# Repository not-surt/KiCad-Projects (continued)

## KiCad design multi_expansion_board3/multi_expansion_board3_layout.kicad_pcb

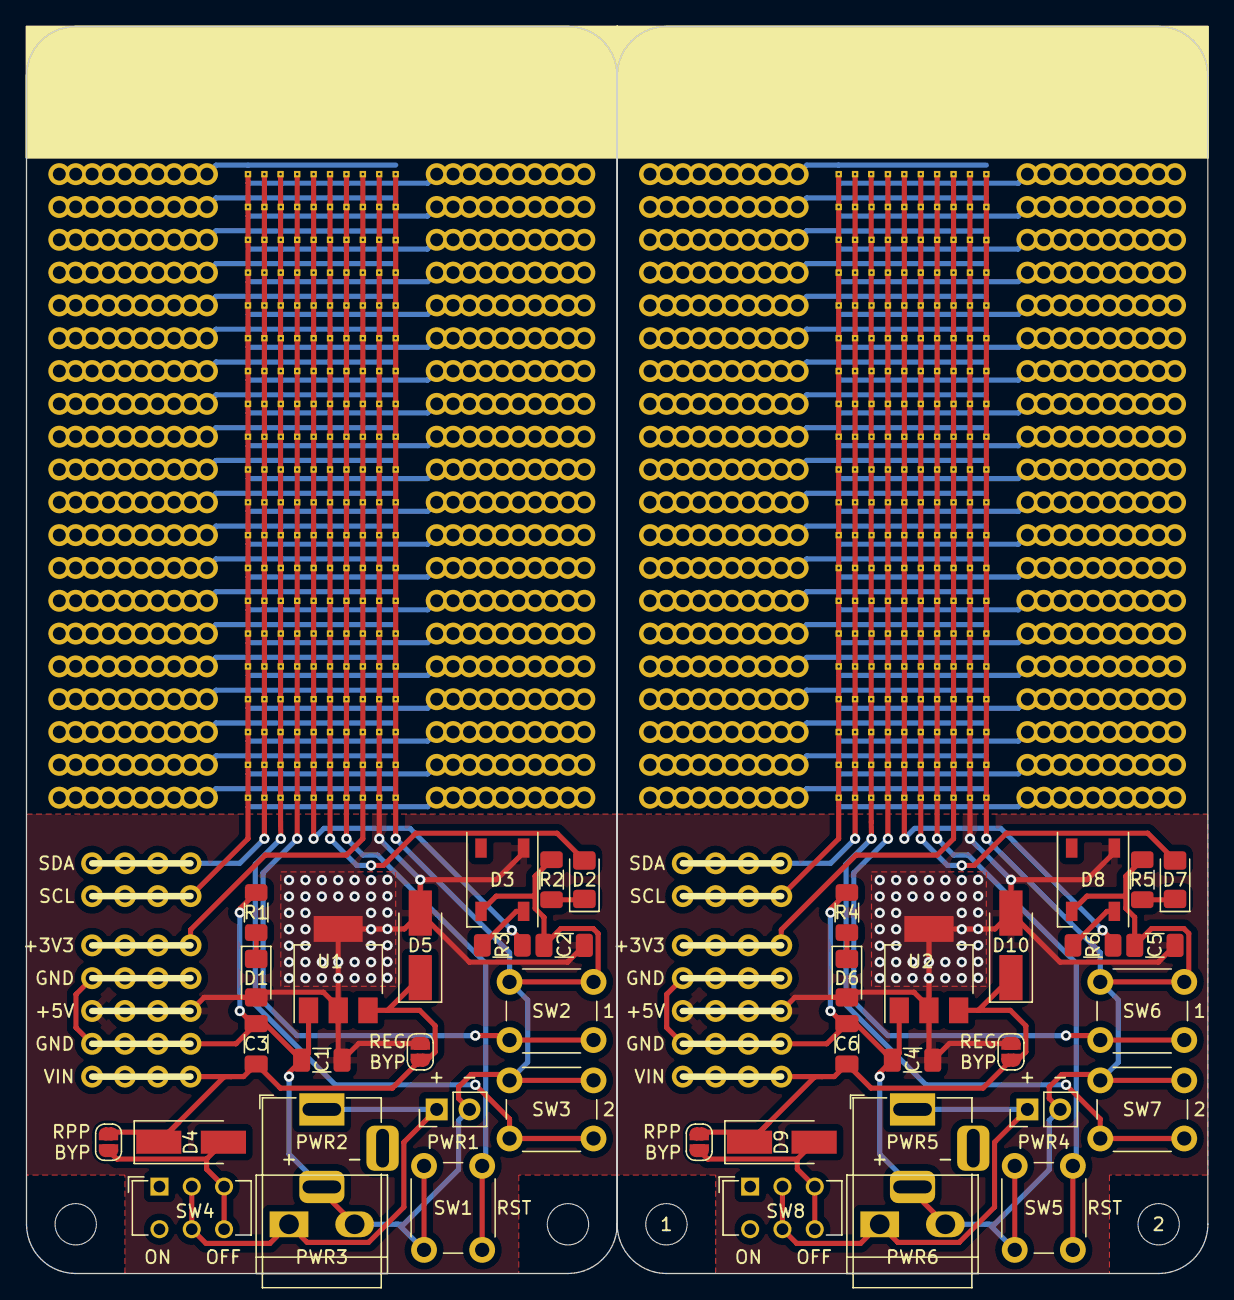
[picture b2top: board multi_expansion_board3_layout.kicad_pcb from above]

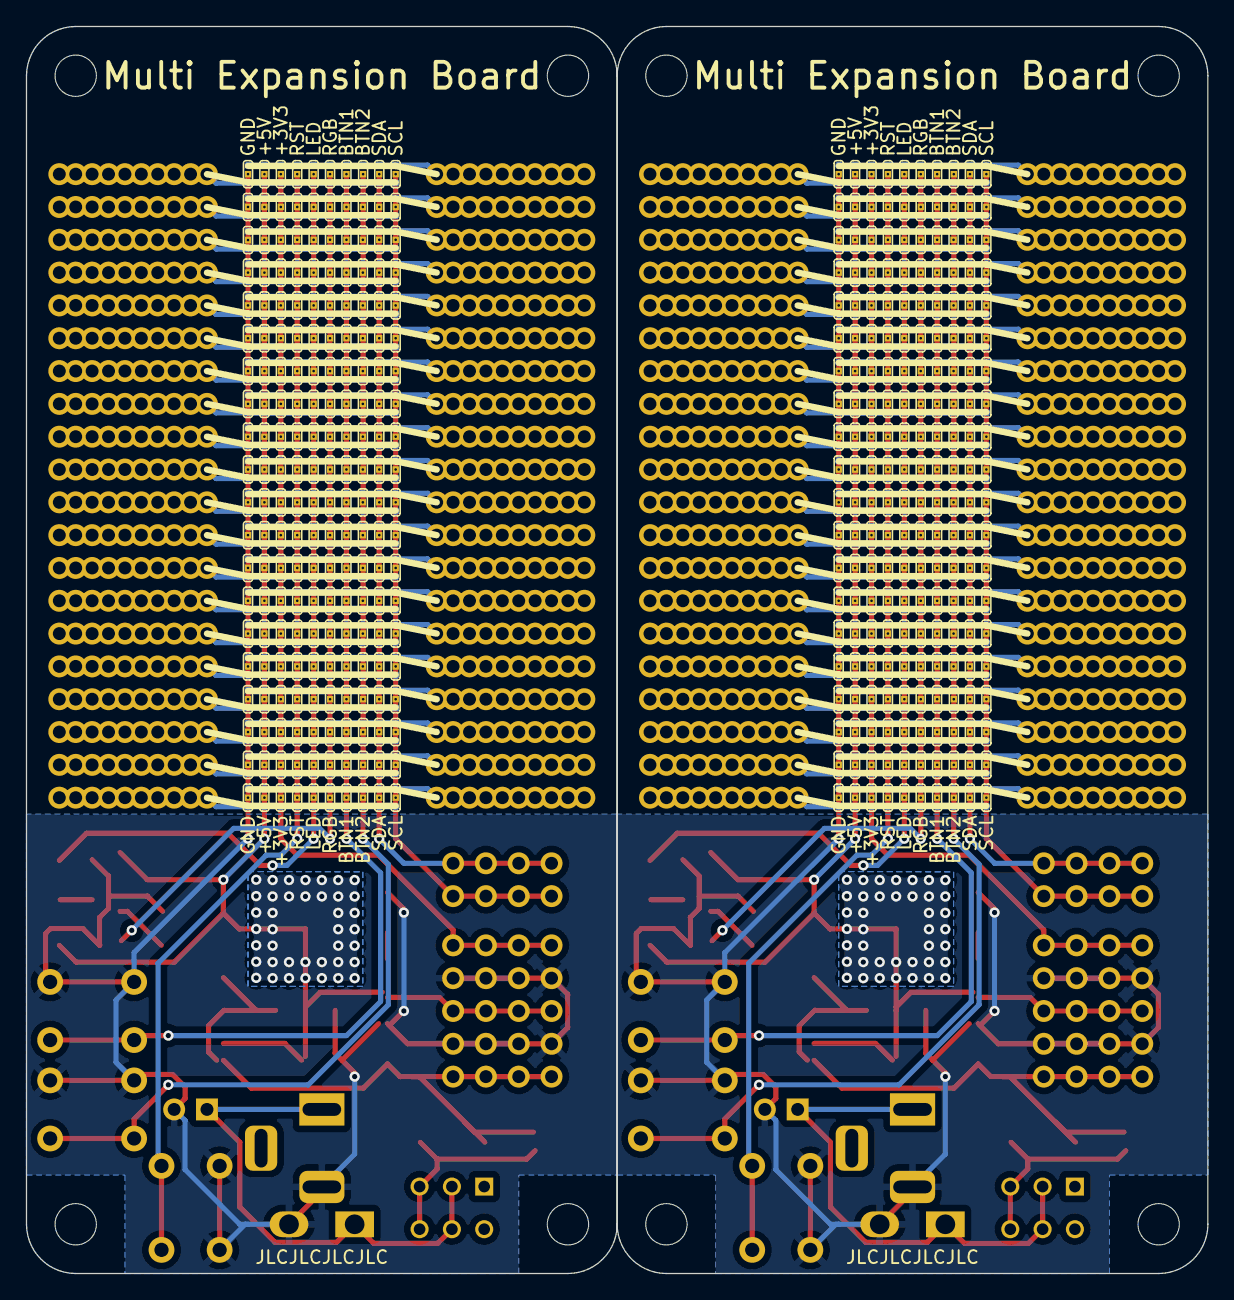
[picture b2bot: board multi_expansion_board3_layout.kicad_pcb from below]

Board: 2 copper layers, 91.4 x 96.5 mm, 500 parts (400 on the bottom side), 56 nets.

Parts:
1, 2, 3, 4: MountingHole_3.2mm_M3
C1, C4: 0.1uF; C_1206_3216Metric_Pad1.33x1.80mm_HandSolder
C2, C3, C5, C6: 10uF; C_1206_3216Metric_Pad1.33x1.80mm_HandSolder
D1, D2, D6, D7: LED; LED_1206_3216Metric_Pad1.42x1.75mm_HandSolder
D3, D8: WS2812B; LED_WS2812B_PLCC4_5.0x5.0mm_P3.2mm
D4, D5, D9, D10: D; D_SMA_Handsoldering
J1, J2, J3, J4, J5, J6, J7, J8, J9, J10, J11, J12, J13, J14, J15, J16, J17, J18, J19, J20, J28, J29, J30, J31, J32, J33, J34, J35, J36, J37, J38, J39, J40, J41, J42, J43, J44, J45, J46, J47: Conn_01x20; PinHeader_1x20_P2.54mm_Vertical_No_Silk
J21, J22, J23, J24, J25, J26, J27, J48, J49, J50, J51, J52, J53, J54: Conn_01x04; PinHeader_1x04_P2.54mm_Vertical_No_Silk
JP1, JP2, JP203, JP204: SolderJumper_2_Open; SolderJumper-2_P1.3mm_Open_RoundedPad1.0x1.5mm
JP3, JP4, JP5, JP6, JP7, JP8, JP9, JP10, JP11, JP12, JP13, JP14, JP15, JP16, JP17, JP18, JP19, JP20, JP21, JP22, JP23, JP24, JP25, JP26, JP27, JP28, JP29, JP30, JP31, JP32, JP33, JP34, JP35, JP36, JP37, JP38, JP39, JP40, JP41, JP42, JP43, JP44, JP45, JP46, JP47, JP48, JP49, JP50, JP51, JP52, JP53, JP54, JP55, JP56, JP57, JP58, JP59, JP60, JP61, JP62, JP63, JP64, JP65, JP66, JP67, JP68, JP69, JP70, JP71, JP72, JP73, JP74, JP75, JP76, JP77, JP78, JP79, JP80, JP81, JP82, JP83, JP84, JP85, JP86, JP87, JP88, JP89, JP90, JP91, JP92, JP93, JP94, JP95, JP96, JP97, JP98, JP99, JP100, JP101, JP102, JP103, JP104, JP105, JP106, JP107, JP108, JP109, JP110, JP111, JP112, JP113, JP114, JP115, JP116, JP117, JP118, JP119, JP120, JP121, JP122, JP123, JP124, JP125, JP126, JP127, JP128, JP129, JP130, JP131, JP132, JP133, JP134, JP135, JP136, JP137, JP138, JP139, JP140, JP141, JP142, JP143, JP144, JP145, JP146, JP147, JP148, JP149, JP150, JP151, JP152, JP153, JP154, JP155, JP156, JP157, JP158, JP159, JP160, JP161, JP162, JP163, JP164, JP165, JP166, JP167, JP168, JP169, JP170, JP171, JP172, JP173, JP174, JP175, JP176, JP177, JP178, JP179, JP180, JP181, JP182, JP183, JP184, JP185, JP186, JP187, JP188, JP189, JP190, JP191, JP192, JP193, JP194, JP195, JP196, JP197, JP198, JP199, JP200, JP201, JP202, JP205, JP206, JP207, JP208, JP209, JP210, JP211, JP212, JP213, JP214, JP215, JP216, JP217, JP218, JP219, JP220, JP221, JP222, JP223, JP224, JP225, JP226, JP227, JP228, JP229, JP230, JP231, JP232, JP233, JP234, JP235, JP236, JP237, JP238, JP239, JP240, JP241, JP242, JP243, JP244, JP245, JP246, JP247, JP248, JP249, JP250, JP251, JP252, JP253, JP254, JP255, JP256, JP257, JP258, JP259, JP260, JP261, JP262, JP263, JP264, JP265, JP266, JP267, JP268, JP269, JP270, JP271, JP272, JP273, JP274, JP275, JP276, JP277, JP278, JP279, JP280, JP281, JP282, JP283, JP284, JP285, JP286, JP287, JP288, JP289, JP290, JP291, JP292, JP293, JP294, JP295, JP296, JP297, JP298, JP299, JP300, JP301, JP302, JP303, JP304, JP305, JP306, JP307, JP308, JP309, JP310, JP311, JP312, JP313, JP314, JP315, JP316, JP317, JP318, JP319, JP320, JP321, JP322, JP323, JP324, JP325, JP326, JP327, JP328, JP329, JP330, JP331, JP332, JP333, JP334, JP335, JP336, JP337, JP338, JP339, JP340, JP341, JP342, JP343, JP344, JP345, JP346, JP347, JP348, JP349, JP350, JP351, JP352, JP353, JP354, JP355, JP356, JP357, JP358, JP359, JP360, JP361, JP362, JP363, JP364, JP365, JP366, JP367, JP368, JP369, JP370, JP371, JP372, JP373, JP374, JP375, JP376, JP377, JP378, JP379, JP380, JP381, JP382, JP383, JP384, JP385, JP386, JP387, JP388, JP389, JP390, JP391, JP392, JP393, JP394, JP395, JP396, JP397, JP398, JP399, JP400, JP401, JP402, JP403, JP404: SolderJumper_3_Open; SolderJumper-mini-3
PWR1, PWR4: Conn_01x02; PinHeader_1x02_P2.54mm_Vertical
PWR2, PWR5: Barrel_Jack; BarrelJack_Horizontal
PWR3, PWR6: Screw_Terminal_01x02; TerminalBlock_bornier-2_P5.08mm
R1, R2, R4, R5: R; R_1206_3216Metric_Pad1.30x1.75mm_HandSolder
R3, R6: 470R; R_1206_3216Metric_Pad1.30x1.75mm_HandSolder
SW1, SW2, SW3, SW5, SW6, SW7: SW_Push; SW_PUSH_6mm
SW4, SW8: SW_SPST; SW_CuK_JS202011CQN_DPDT_Straight
U1, U2: AMS1117-5.0; SOT-223-3_TabPin2

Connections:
/+3V3: J25.1, J25.2, J25.3, J25.4, J52.1, J52.2, J52.3, J52.4, JP43.2 (C), JP44.2 (C), JP45.2 (C), JP46.2 (C), JP47.2 (C), JP48.2 (C), JP49.2 (C), JP50.2 (C), JP51.2 (C), JP52.2 (C), JP53.2 (C), JP54.2 (C), JP55.2 (C), JP56.2 (C), JP57.2 (C), JP58.2 (C), JP59.2 (C), JP60.2 (C), JP61.2 (C), JP62.2 (C), JP245.2 (C), JP246.2 (C), JP247.2 (C), JP248.2 (C), JP249.2 (C), JP250.2 (C), JP251.2 (C), JP252.2 (C), JP253.2 (C), JP254.2 (C), JP255.2 (C), JP256.2 (C), JP257.2 (C), JP258.2 (C), JP259.2 (C), JP260.2 (C), JP261.2 (C), JP262.2 (C), JP263.2 (C), JP264.2 (C)
/+5V: C1.2, C2.1, C4.2, C5.1, D1.2 (A), D3.1 (VDD), D5.2 (A), D6.2 (A), D8.1 (VDD), D10.2 (A), J24.1, J24.2, J24.3, J24.4, J51.1, J51.2, J51.3, J51.4, JP2.2 (B), JP3.2 (C), JP4.2 (C), JP5.2 (C), JP6.2 (C), JP7.2 (C), JP8.2 (C), JP9.2 (C), JP10.2 (C), JP11.2 (C), JP12.2 (C), JP13.2 (C), JP14.2 (C), JP15.2 (C), JP16.2 (C), JP17.2 (C), JP18.2 (C), JP19.2 (C), JP20.2 (C), JP21.2 (C), JP22.2 (C), JP204.2 (B), JP205.2 (C), JP206.2 (C), JP207.2 (C), JP208.2 (C), JP209.2 (C), JP210.2 (C), JP211.2 (C), JP212.2 (C), JP213.2 (C), JP214.2 (C), JP215.2 (C), JP216.2 (C), JP217.2 (C), JP218.2 (C), JP219.2 (C), JP220.2 (C), JP221.2 (C), JP222.2 (C), JP223.2 (C), JP224.2 (C), U1.2 (VO), U2.2 (VO)
/BTN1: JP83.2 (C), JP84.2 (C), JP85.2 (C), JP86.2 (C), JP87.2 (C), JP88.2 (C), JP89.2 (C), JP90.2 (C), JP91.2 (C), JP92.2 (C), JP93.2 (C), JP94.2 (C), JP95.2 (C), JP96.2 (C), JP97.2 (C), JP98.2 (C), JP99.2 (C), JP100.2 (C), JP101.2 (C), JP102.2 (C), JP285.2 (C), JP286.2 (C), JP287.2 (C), JP288.2 (C), JP289.2 (C), JP290.2 (C), JP291.2 (C), JP292.2 (C), JP293.2 (C), JP294.2 (C), JP295.2 (C), JP296.2 (C), JP297.2 (C), JP298.2 (C), JP299.2 (C), JP300.2 (C), JP301.2 (C), JP302.2 (C), JP303.2 (C), JP304.2 (C), SW2.2, SW6.2
/BTN2: JP183.2 (C), JP184.2 (C), JP185.2 (C), JP186.2 (C), JP187.2 (C), JP188.2 (C), JP189.2 (C), JP190.2 (C), JP191.2 (C), JP192.2 (C), JP193.2 (C), JP194.2 (C), JP195.2 (C), JP196.2 (C), JP197.2 (C), JP198.2 (C), JP199.2 (C), JP200.2 (C), JP201.2 (C), JP202.2 (C), JP385.2 (C), JP386.2 (C), JP387.2 (C), JP388.2 (C), JP389.2 (C), JP390.2 (C), JP391.2 (C), JP392.2 (C), JP393.2 (C), JP394.2 (C), JP395.2 (C), JP396.2 (C), JP397.2 (C), JP398.2 (C), JP399.2 (C), JP400.2 (C), JP401.2 (C), JP402.2 (C), JP403.2 (C), JP404.2 (C), SW3.2, SW7.2
/LED: D2.2 (A), D7.2 (A), JP63.2 (C), JP64.2 (C), JP65.2 (C), JP66.2 (C), JP67.2 (C), JP68.2 (C), JP69.2 (C), JP70.2 (C), JP71.2 (C), JP72.2 (C), JP73.2 (C), JP74.2 (C), JP75.2 (C), JP76.2 (C), JP77.2 (C), JP78.2 (C), JP79.2 (C), JP80.2 (C), JP81.2 (C), JP82.2 (C), JP265.2 (C), JP266.2 (C), JP267.2 (C), JP268.2 (C), JP269.2 (C), JP270.2 (C), JP271.2 (C), JP272.2 (C), JP273.2 (C), JP274.2 (C), JP275.2 (C), JP276.2 (C), JP277.2 (C), JP278.2 (C), JP279.2 (C), JP280.2 (C), JP281.2 (C), JP282.2 (C), JP283.2 (C), JP284.2 (C)
/RGB: JP103.2 (C), JP104.2 (C), JP105.2 (C), JP106.2 (C), JP107.2 (C), JP108.2 (C), JP109.2 (C), JP110.2 (C), JP111.2 (C), JP112.2 (C), JP113.2 (C), JP114.2 (C), JP115.2 (C), JP116.2 (C), JP117.2 (C), JP118.2 (C), JP119.2 (C), JP120.2 (C), JP121.2 (C), JP122.2 (C), JP305.2 (C), JP306.2 (C), JP307.2 (C), JP308.2 (C), JP309.2 (C), JP310.2 (C), JP311.2 (C), JP312.2 (C), JP313.2 (C), JP314.2 (C), JP315.2 (C), JP316.2 (C), JP317.2 (C), JP318.2 (C), JP319.2 (C), JP320.2 (C), JP321.2 (C), JP322.2 (C), JP323.2 (C), JP324.2 (C), R3.1, R6.1
/RST: JP163.2 (C), JP164.2 (C), JP165.2 (C), JP166.2 (C), JP167.2 (C), JP168.2 (C), JP169.2 (C), JP170.2 (C), JP171.2 (C), JP172.2 (C), JP173.2 (C), JP174.2 (C), JP175.2 (C), JP176.2 (C), JP177.2 (C), JP178.2 (C), JP179.2 (C), JP180.2 (C), JP181.2 (C), JP182.2 (C), JP365.2 (C), JP366.2 (C), JP367.2 (C), JP368.2 (C), JP369.2 (C), JP370.2 (C), JP371.2 (C), JP372.2 (C), JP373.2 (C), JP374.2 (C), JP375.2 (C), JP376.2 (C), JP377.2 (C), JP378.2 (C), JP379.2 (C), JP380.2 (C), JP381.2 (C), JP382.2 (C), JP383.2 (C), JP384.2 (C), SW1.2, SW5.2
/SCL: J27.1, J27.2, J27.3, J27.4, J54.1, J54.2, J54.3, J54.4, JP143.2 (C), JP144.2 (C), JP145.2 (C), JP146.2 (C), JP147.2 (C), JP148.2 (C), JP149.2 (C), JP150.2 (C), JP151.2 (C), JP152.2 (C), JP153.2 (C), JP154.2 (C), JP155.2 (C), JP156.2 (C), JP157.2 (C), JP158.2 (C), JP159.2 (C), JP160.2 (C), JP161.2 (C), JP162.2 (C), JP345.2 (C), JP346.2 (C), JP347.2 (C), JP348.2 (C), JP349.2 (C), JP350.2 (C), JP351.2 (C), JP352.2 (C), JP353.2 (C), JP354.2 (C), JP355.2 (C), JP356.2 (C), JP357.2 (C), JP358.2 (C), JP359.2 (C), JP360.2 (C), JP361.2 (C), JP362.2 (C), JP363.2 (C), JP364.2 (C)
/SDA: J26.1, J26.2, J26.3, J26.4, J53.1, J53.2, J53.3, J53.4, JP123.2 (C), JP124.2 (C), JP125.2 (C), JP126.2 (C), JP127.2 (C), JP128.2 (C), JP129.2 (C), JP130.2 (C), JP131.2 (C), JP132.2 (C), JP133.2 (C), JP134.2 (C), JP135.2 (C), JP136.2 (C), JP137.2 (C), JP138.2 (C), JP139.2 (C), JP140.2 (C), JP141.2 (C), JP142.2 (C), JP325.2 (C), JP326.2 (C), JP327.2 (C), JP328.2 (C), JP329.2 (C), JP330.2 (C), JP331.2 (C), JP332.2 (C), JP333.2 (C), JP334.2 (C), JP335.2 (C), JP336.2 (C), JP337.2 (C), JP338.2 (C), JP339.2 (C), JP340.2 (C), JP341.2 (C), JP342.2 (C), JP343.2 (C), JP344.2 (C)
/VIN: C3.1, C6.1, D4.1 (K), D5.1 (K), D9.1 (K), D10.1 (K), J23.1, J23.2, J23.3, J23.4, J50.1, J50.2, J50.3, J50.4, JP1.2 (B), JP2.1 (A), JP203.2 (B), JP204.1 (A), U1.3 (VI), U2.3 (VI)
GND: C1.1, C2.2, C3.2, C4.1, C5.2, C6.2, D3.3 (VSS), D8.3 (VSS), J21.1, J21.2, J21.3, J21.4, J22.1, J22.2, J22.3, J22.4, J48.1, J48.2, J48.3, J48.4, J49.1, J49.2, J49.3, J49.4, JP23.2 (C), JP24.2 (C), JP25.2 (C), JP26.2 (C), JP27.2 (C), JP28.2 (C), JP29.2 (C), JP30.2 (C), JP31.2 (C), JP32.2 (C), JP33.2 (C), JP34.2 (C), JP35.2 (C), JP36.2 (C), JP37.2 (C), JP38.2 (C), JP39.2 (C), JP40.2 (C), JP41.2 (C), JP42.2 (C), JP225.2 (C), JP226.2 (C), JP227.2 (C), JP228.2 (C), JP229.2 (C), JP230.2 (C), JP231.2 (C), JP232.2 (C), JP233.2 (C), JP234.2 (C), JP235.2 (C), JP236.2 (C), JP237.2 (C), JP238.2 (C), JP239.2 (C), JP240.2 (C), JP241.2 (C), JP242.2 (C), JP243.2 (C), JP244.2 (C), PWR1.2, PWR2.2, PWR3.2, PWR4.2, PWR5.2, PWR6.2, R1.2, R2.2, R4.2, R5.2, SW1.1, SW2.1, SW3.1, SW5.1, SW6.1, SW7.1, U1.1 (GND), U2.1 (GND)
unnamed: D1.1 (K), D6.1 (K), R1.1, R4.1
unnamed: D2.1 (K), D7.1 (K), R2.1, R5.1
unnamed: D3.4 (DIN), D8.4 (DIN), R3.2, R6.2
unnamed: D4.2 (A), D9.2 (A), JP1.1 (A), JP203.1 (A), SW4.3 (C), SW4.6 (C), SW8.3 (C), SW8.6 (C)
unnamed: PWR1.1, PWR2.1, PWR3.1, PWR4.1, PWR5.1, PWR6.1, SW4.2 (B), SW4.5 (B), SW8.2 (B), SW8.5 (B)
Pin_1: J1.1, J2.1, J3.1, J4.1, J5.1, J6.1, J7.1, J8.1, J9.1, J10.1, J28.1, J29.1, J30.1, J31.1, J32.1, J33.1, J34.1, J35.1, J36.1, J37.1, JP3.1 (A), JP23.1 (A), JP43.1 (A), JP63.1 (A), JP83.1 (A), JP103.1 (A), JP123.1 (A), JP143.1 (A), JP163.1 (A), JP183.1 (A), JP205.1 (A), JP225.1 (A), JP245.1 (A), JP265.1 (A), JP285.1 (A), JP305.1 (A), JP325.1 (A), JP345.1 (A), JP365.1 (A), JP385.1 (A)
Pin_2: J1.2, J2.2, J3.2, J4.2, J5.2, J6.2, J7.2, J8.2, J9.2, J10.2, J28.2, J29.2, J30.2, J31.2, J32.2, J33.2, J34.2, J35.2, J36.2, J37.2, JP4.1 (A), JP24.1 (A), JP44.1 (A), JP64.1 (A), JP84.1 (A), JP104.1 (A), JP124.1 (A), JP144.1 (A), JP164.1 (A), JP184.1 (A), JP206.1 (A), JP226.1 (A), JP246.1 (A), JP266.1 (A), JP286.1 (A), JP306.1 (A), JP326.1 (A), JP346.1 (A), JP366.1 (A), JP386.1 (A)
Pin_3: J1.3, J2.3, J3.3, J4.3, J5.3, J6.3, J7.3, J8.3, J9.3, J10.3, J28.3, J29.3, J30.3, J31.3, J32.3, J33.3, J34.3, J35.3, J36.3, J37.3, JP5.1 (A), JP25.1 (A), JP45.1 (A), JP65.1 (A), JP85.1 (A), JP105.1 (A), JP125.1 (A), JP145.1 (A), JP165.1 (A), JP185.1 (A), JP207.1 (A), JP227.1 (A), JP247.1 (A), JP267.1 (A), JP287.1 (A), JP307.1 (A), JP327.1 (A), JP347.1 (A), JP367.1 (A), JP387.1 (A)
Pin_4: J1.4, J2.4, J3.4, J4.4, J5.4, J6.4, J7.4, J8.4, J9.4, J10.4, J28.4, J29.4, J30.4, J31.4, J32.4, J33.4, J34.4, J35.4, J36.4, J37.4, JP6.1 (A), JP26.1 (A), JP46.1 (A), JP66.1 (A), JP86.1 (A), JP106.1 (A), JP126.1 (A), JP146.1 (A), JP166.1 (A), JP186.1 (A), JP208.1 (A), JP228.1 (A), JP248.1 (A), JP268.1 (A), JP288.1 (A), JP308.1 (A), JP328.1 (A), JP348.1 (A), JP368.1 (A), JP388.1 (A)
Pin_5: J1.5, J2.5, J3.5, J4.5, J5.5, J6.5, J7.5, J8.5, J9.5, J10.5, J28.5, J29.5, J30.5, J31.5, J32.5, J33.5, J34.5, J35.5, J36.5, J37.5, JP7.1 (A), JP27.1 (A), JP47.1 (A), JP67.1 (A), JP87.1 (A), JP107.1 (A), JP127.1 (A), JP147.1 (A), JP167.1 (A), JP187.1 (A), JP209.1 (A), JP229.1 (A), JP249.1 (A), JP269.1 (A), JP289.1 (A), JP309.1 (A), JP329.1 (A), JP349.1 (A), JP369.1 (A), JP389.1 (A)
Pin_6: J1.6, J2.6, J3.6, J4.6, J5.6, J6.6, J7.6, J8.6, J9.6, J10.6, J28.6, J29.6, J30.6, J31.6, J32.6, J33.6, J34.6, J35.6, J36.6, J37.6, JP8.1 (A), JP28.1 (A), JP48.1 (A), JP68.1 (A), JP88.1 (A), JP108.1 (A), JP128.1 (A), JP148.1 (A), JP168.1 (A), JP188.1 (A), JP210.1 (A), JP230.1 (A), JP250.1 (A), JP270.1 (A), JP290.1 (A), JP310.1 (A), JP330.1 (A), JP350.1 (A), JP370.1 (A), JP390.1 (A)
Pin_7: J1.7, J2.7, J3.7, J4.7, J5.7, J6.7, J7.7, J8.7, J9.7, J10.7, J28.7, J29.7, J30.7, J31.7, J32.7, J33.7, J34.7, J35.7, J36.7, J37.7, JP9.1 (A), JP29.1 (A), JP49.1 (A), JP69.1 (A), JP89.1 (A), JP109.1 (A), JP129.1 (A), JP149.1 (A), JP169.1 (A), JP189.1 (A), JP211.1 (A), JP231.1 (A), JP251.1 (A), JP271.1 (A), JP291.1 (A), JP311.1 (A), JP331.1 (A), JP351.1 (A), JP371.1 (A), JP391.1 (A)
Pin_8: J1.8, J2.8, J3.8, J4.8, J5.8, J6.8, J7.8, J8.8, J9.8, J10.8, J28.8, J29.8, J30.8, J31.8, J32.8, J33.8, J34.8, J35.8, J36.8, J37.8, JP10.1 (A), JP30.1 (A), JP50.1 (A), JP70.1 (A), JP90.1 (A), JP110.1 (A), JP130.1 (A), JP150.1 (A), JP170.1 (A), JP190.1 (A), JP212.1 (A), JP232.1 (A), JP252.1 (A), JP272.1 (A), JP292.1 (A), JP312.1 (A), JP332.1 (A), JP352.1 (A), JP372.1 (A), JP392.1 (A)
Pin_9: J1.9, J2.9, J3.9, J4.9, J5.9, J6.9, J7.9, J8.9, J9.9, J10.9, J28.9, J29.9, J30.9, J31.9, J32.9, J33.9, J34.9, J35.9, J36.9, J37.9, JP11.1 (A), JP31.1 (A), JP51.1 (A), JP71.1 (A), JP91.1 (A), JP111.1 (A), JP131.1 (A), JP151.1 (A), JP171.1 (A), JP191.1 (A), JP213.1 (A), JP233.1 (A), JP253.1 (A), JP273.1 (A), JP293.1 (A), JP313.1 (A), JP333.1 (A), JP353.1 (A), JP373.1 (A), JP393.1 (A)
Pin_10: J1.10, J2.10, J3.10, J4.10, J5.10, J6.10, J7.10, J8.10, J9.10, J10.10, J28.10, J29.10, J30.10, J31.10, J32.10, J33.10, J34.10, J35.10, J36.10, J37.10, JP12.1 (A), JP32.1 (A), JP52.1 (A), JP72.1 (A), JP92.1 (A), JP112.1 (A), JP132.1 (A), JP152.1 (A), JP172.1 (A), JP192.1 (A), JP214.1 (A), JP234.1 (A), JP254.1 (A), JP274.1 (A), JP294.1 (A), JP314.1 (A), JP334.1 (A), JP354.1 (A), JP374.1 (A), JP394.1 (A)
Pin_11: J1.11, J2.11, J3.11, J4.11, J5.11, J6.11, J7.11, J8.11, J9.11, J10.11, J28.11, J29.11, J30.11, J31.11, J32.11, J33.11, J34.11, J35.11, J36.11, J37.11, JP13.1 (A), JP33.1 (A), JP53.1 (A), JP73.1 (A), JP93.1 (A), JP113.1 (A), JP133.1 (A), JP153.1 (A), JP173.1 (A), JP193.1 (A), JP215.1 (A), JP235.1 (A), JP255.1 (A), JP275.1 (A), JP295.1 (A), JP315.1 (A), JP335.1 (A), JP355.1 (A), JP375.1 (A), JP395.1 (A)
Pin_12: J1.12, J2.12, J3.12, J4.12, J5.12, J6.12, J7.12, J8.12, J9.12, J10.12, J28.12, J29.12, J30.12, J31.12, J32.12, J33.12, J34.12, J35.12, J36.12, J37.12, JP14.1 (A), JP34.1 (A), JP54.1 (A), JP74.1 (A), JP94.1 (A), JP114.1 (A), JP134.1 (A), JP154.1 (A), JP174.1 (A), JP194.1 (A), JP216.1 (A), JP236.1 (A), JP256.1 (A), JP276.1 (A), JP296.1 (A), JP316.1 (A), JP336.1 (A), JP356.1 (A), JP376.1 (A), JP396.1 (A)
Pin_13: J1.13, J2.13, J3.13, J4.13, J5.13, J6.13, J7.13, J8.13, J9.13, J10.13, J28.13, J29.13, J30.13, J31.13, J32.13, J33.13, J34.13, J35.13, J36.13, J37.13, JP15.1 (A), JP35.1 (A), JP55.1 (A), JP75.1 (A), JP95.1 (A), JP115.1 (A), JP135.1 (A), JP155.1 (A), JP175.1 (A), JP195.1 (A), JP217.1 (A), JP237.1 (A), JP257.1 (A), JP277.1 (A), JP297.1 (A), JP317.1 (A), JP337.1 (A), JP357.1 (A), JP377.1 (A), JP397.1 (A)
Pin_14: J1.14, J2.14, J3.14, J4.14, J5.14, J6.14, J7.14, J8.14, J9.14, J10.14, J28.14, J29.14, J30.14, J31.14, J32.14, J33.14, J34.14, J35.14, J36.14, J37.14, JP16.1 (A), JP36.1 (A), JP56.1 (A), JP76.1 (A), JP96.1 (A), JP116.1 (A), JP136.1 (A), JP156.1 (A), JP176.1 (A), JP196.1 (A), JP218.1 (A), JP238.1 (A), JP258.1 (A), JP278.1 (A), JP298.1 (A), JP318.1 (A), JP338.1 (A), JP358.1 (A), JP378.1 (A), JP398.1 (A)
Pin_15: J1.15, J2.15, J3.15, J4.15, J5.15, J6.15, J7.15, J8.15, J9.15, J10.15, J28.15, J29.15, J30.15, J31.15, J32.15, J33.15, J34.15, J35.15, J36.15, J37.15, JP17.1 (A), JP37.1 (A), JP57.1 (A), JP77.1 (A), JP97.1 (A), JP117.1 (A), JP137.1 (A), JP157.1 (A), JP177.1 (A), JP197.1 (A), JP219.1 (A), JP239.1 (A), JP259.1 (A), JP279.1 (A), JP299.1 (A), JP319.1 (A), JP339.1 (A), JP359.1 (A), JP379.1 (A), JP399.1 (A)
Pin_16: J1.16, J2.16, J3.16, J4.16, J5.16, J6.16, J7.16, J8.16, J9.16, J10.16, J28.16, J29.16, J30.16, J31.16, J32.16, J33.16, J34.16, J35.16, J36.16, J37.16, JP18.1 (A), JP38.1 (A), JP58.1 (A), JP78.1 (A), JP98.1 (A), JP118.1 (A), JP138.1 (A), JP158.1 (A), JP178.1 (A), JP198.1 (A), JP220.1 (A), JP240.1 (A), JP260.1 (A), JP280.1 (A), JP300.1 (A), JP320.1 (A), JP340.1 (A), JP360.1 (A), JP380.1 (A), JP400.1 (A)
Pin_17: J1.17, J2.17, J3.17, J4.17, J5.17, J6.17, J7.17, J8.17, J9.17, J10.17, J28.17, J29.17, J30.17, J31.17, J32.17, J33.17, J34.17, J35.17, J36.17, J37.17, JP19.1 (A), JP39.1 (A), JP59.1 (A), JP79.1 (A), JP99.1 (A), JP119.1 (A), JP139.1 (A), JP159.1 (A), JP179.1 (A), JP199.1 (A), JP221.1 (A), JP241.1 (A), JP261.1 (A), JP281.1 (A), JP301.1 (A), JP321.1 (A), JP341.1 (A), JP361.1 (A), JP381.1 (A), JP401.1 (A)
Pin_18: J1.18, J2.18, J3.18, J4.18, J5.18, J6.18, J7.18, J8.18, J9.18, J10.18, J28.18, J29.18, J30.18, J31.18, J32.18, J33.18, J34.18, J35.18, J36.18, J37.18, JP20.1 (A), JP40.1 (A), JP60.1 (A), JP80.1 (A), JP100.1 (A), JP120.1 (A), JP140.1 (A), JP160.1 (A), JP180.1 (A), JP200.1 (A), JP222.1 (A), JP242.1 (A), JP262.1 (A), JP282.1 (A), JP302.1 (A), JP322.1 (A), JP342.1 (A), JP362.1 (A), JP382.1 (A), JP402.1 (A)
Pin_19: J1.19, J2.19, J3.19, J4.19, J5.19, J6.19, J7.19, J8.19, J9.19, J10.19, J28.19, J29.19, J30.19, J31.19, J32.19, J33.19, J34.19, J35.19, J36.19, J37.19, JP21.1 (A), JP41.1 (A), JP61.1 (A), JP81.1 (A), JP101.1 (A), JP121.1 (A), JP141.1 (A), JP161.1 (A), JP181.1 (A), JP201.1 (A), JP223.1 (A), JP243.1 (A), JP263.1 (A), JP283.1 (A), JP303.1 (A), JP323.1 (A), JP343.1 (A), JP363.1 (A), JP383.1 (A), JP403.1 (A)
Pin_20: J1.20, J2.20, J3.20, J4.20, J5.20, J6.20, J7.20, J8.20, J9.20, J10.20, J28.20, J29.20, J30.20, J31.20, J32.20, J33.20, J34.20, J35.20, J36.20, J37.20, JP22.1 (A), JP42.1 (A), JP62.1 (A), JP82.1 (A), JP102.1 (A), JP122.1 (A), JP142.1 (A), JP162.1 (A), JP182.1 (A), JP202.1 (A), JP224.1 (A), JP244.1 (A), JP264.1 (A), JP284.1 (A), JP304.1 (A), JP324.1 (A), JP344.1 (A), JP364.1 (A), JP384.1 (A), JP404.1 (A)
Pin_21: J11.20, J12.20, J13.20, J14.20, J15.20, J16.20, J17.20, J18.20, J19.20, J20.20, J38.20, J39.20, J40.20, J41.20, J42.20, J43.20, J44.20, J45.20, J46.20, J47.20, JP22.3 (B), JP42.3 (B), JP62.3 (B), JP82.3 (B), JP102.3 (B), JP122.3 (B), JP142.3 (B), JP162.3 (B), JP182.3 (B), JP202.3 (B), JP224.3 (B), JP244.3 (B), JP264.3 (B), JP284.3 (B), JP304.3 (B), JP324.3 (B), JP344.3 (B), JP364.3 (B), JP384.3 (B), JP404.3 (B)
Pin_22: J11.19, J12.19, J13.19, J14.19, J15.19, J16.19, J17.19, J18.19, J19.19, J20.19, J38.19, J39.19, J40.19, J41.19, J42.19, J43.19, J44.19, J45.19, J46.19, J47.19, JP21.3 (B), JP41.3 (B), JP61.3 (B), JP81.3 (B), JP101.3 (B), JP121.3 (B), JP141.3 (B), JP161.3 (B), JP181.3 (B), JP201.3 (B), JP223.3 (B), JP243.3 (B), JP263.3 (B), JP283.3 (B), JP303.3 (B), JP323.3 (B), JP343.3 (B), JP363.3 (B), JP383.3 (B), JP403.3 (B)
Pin_23: J11.18, J12.18, J13.18, J14.18, J15.18, J16.18, J17.18, J18.18, J19.18, J20.18, J38.18, J39.18, J40.18, J41.18, J42.18, J43.18, J44.18, J45.18, J46.18, J47.18, JP20.3 (B), JP40.3 (B), JP60.3 (B), JP80.3 (B), JP100.3 (B), JP120.3 (B), JP140.3 (B), JP160.3 (B), JP180.3 (B), JP200.3 (B), JP222.3 (B), JP242.3 (B), JP262.3 (B), JP282.3 (B), JP302.3 (B), JP322.3 (B), JP342.3 (B), JP362.3 (B), JP382.3 (B), JP402.3 (B)
Pin_24: J11.17, J12.17, J13.17, J14.17, J15.17, J16.17, J17.17, J18.17, J19.17, J20.17, J38.17, J39.17, J40.17, J41.17, J42.17, J43.17, J44.17, J45.17, J46.17, J47.17, JP19.3 (B), JP39.3 (B), JP59.3 (B), JP79.3 (B), JP99.3 (B), JP119.3 (B), JP139.3 (B), JP159.3 (B), JP179.3 (B), JP199.3 (B), JP221.3 (B), JP241.3 (B), JP261.3 (B), JP281.3 (B), JP301.3 (B), JP321.3 (B), JP341.3 (B), JP361.3 (B), JP381.3 (B), JP401.3 (B)
Pin_25: J11.16, J12.16, J13.16, J14.16, J15.16, J16.16, J17.16, J18.16, J19.16, J20.16, J38.16, J39.16, J40.16, J41.16, J42.16, J43.16, J44.16, J45.16, J46.16, J47.16, JP18.3 (B), JP38.3 (B), JP58.3 (B), JP78.3 (B), JP98.3 (B), JP118.3 (B), JP138.3 (B), JP158.3 (B), JP178.3 (B), JP198.3 (B), JP220.3 (B), JP240.3 (B), JP260.3 (B), JP280.3 (B), JP300.3 (B), JP320.3 (B), JP340.3 (B), JP360.3 (B), JP380.3 (B), JP400.3 (B)
Pin_26: J11.15, J12.15, J13.15, J14.15, J15.15, J16.15, J17.15, J18.15, J19.15, J20.15, J38.15, J39.15, J40.15, J41.15, J42.15, J43.15, J44.15, J45.15, J46.15, J47.15, JP17.3 (B), JP37.3 (B), JP57.3 (B), JP77.3 (B), JP97.3 (B), JP117.3 (B), JP137.3 (B), JP157.3 (B), JP177.3 (B), JP197.3 (B), JP219.3 (B), JP239.3 (B), JP259.3 (B), JP279.3 (B), JP299.3 (B), JP319.3 (B), JP339.3 (B), JP359.3 (B), JP379.3 (B), JP399.3 (B)
Pin_27: J11.14, J12.14, J13.14, J14.14, J15.14, J16.14, J17.14, J18.14, J19.14, J20.14, J38.14, J39.14, J40.14, J41.14, J42.14, J43.14, J44.14, J45.14, J46.14, J47.14, JP16.3 (B), JP36.3 (B), JP56.3 (B), JP76.3 (B), JP96.3 (B), JP116.3 (B), JP136.3 (B), JP156.3 (B), JP176.3 (B), JP196.3 (B), JP218.3 (B), JP238.3 (B), JP258.3 (B), JP278.3 (B), JP298.3 (B), JP318.3 (B), JP338.3 (B), JP358.3 (B), JP378.3 (B), JP398.3 (B)
Pin_28: J11.13, J12.13, J13.13, J14.13, J15.13, J16.13, J17.13, J18.13, J19.13, J20.13, J38.13, J39.13, J40.13, J41.13, J42.13, J43.13, J44.13, J45.13, J46.13, J47.13, JP15.3 (B), JP35.3 (B), JP55.3 (B), JP75.3 (B), JP95.3 (B), JP115.3 (B), JP135.3 (B), JP155.3 (B), JP175.3 (B), JP195.3 (B), JP217.3 (B), JP237.3 (B), JP257.3 (B), JP277.3 (B), JP297.3 (B), JP317.3 (B), JP337.3 (B), JP357.3 (B), JP377.3 (B), JP397.3 (B)
Pin_29: J11.12, J12.12, J13.12, J14.12, J15.12, J16.12, J17.12, J18.12, J19.12, J20.12, J38.12, J39.12, J40.12, J41.12, J42.12, J43.12, J44.12, J45.12, J46.12, J47.12, JP14.3 (B), JP34.3 (B), JP54.3 (B), JP74.3 (B), JP94.3 (B), JP114.3 (B), JP134.3 (B), JP154.3 (B), JP174.3 (B), JP194.3 (B), JP216.3 (B), JP236.3 (B), JP256.3 (B), JP276.3 (B), JP296.3 (B), JP316.3 (B), JP336.3 (B), JP356.3 (B), JP376.3 (B), JP396.3 (B)
Pin_30: J11.11, J12.11, J13.11, J14.11, J15.11, J16.11, J17.11, J18.11, J19.11, J20.11, J38.11, J39.11, J40.11, J41.11, J42.11, J43.11, J44.11, J45.11, J46.11, J47.11, JP13.3 (B), JP33.3 (B), JP53.3 (B), JP73.3 (B), JP93.3 (B), JP113.3 (B), JP133.3 (B), JP153.3 (B), JP173.3 (B), JP193.3 (B), JP215.3 (B), JP235.3 (B), JP255.3 (B), JP275.3 (B), JP295.3 (B), JP315.3 (B), JP335.3 (B), JP355.3 (B), JP375.3 (B), JP395.3 (B)
Pin_31: J11.10, J12.10, J13.10, J14.10, J15.10, J16.10, J17.10, J18.10, J19.10, J20.10, J38.10, J39.10, J40.10, J41.10, J42.10, J43.10, J44.10, J45.10, J46.10, J47.10, JP12.3 (B), JP32.3 (B), JP52.3 (B), JP72.3 (B), JP92.3 (B), JP112.3 (B), JP132.3 (B), JP152.3 (B), JP172.3 (B), JP192.3 (B), JP214.3 (B), JP234.3 (B), JP254.3 (B), JP274.3 (B), JP294.3 (B), JP314.3 (B), JP334.3 (B), JP354.3 (B), JP374.3 (B), JP394.3 (B)
Pin_32: J11.9, J12.9, J13.9, J14.9, J15.9, J16.9, J17.9, J18.9, J19.9, J20.9, J38.9, J39.9, J40.9, J41.9, J42.9, J43.9, J44.9, J45.9, J46.9, J47.9, JP11.3 (B), JP31.3 (B), JP51.3 (B), JP71.3 (B), JP91.3 (B), JP111.3 (B), JP131.3 (B), JP151.3 (B), JP171.3 (B), JP191.3 (B), JP213.3 (B), JP233.3 (B), JP253.3 (B), JP273.3 (B), JP293.3 (B), JP313.3 (B), JP333.3 (B), JP353.3 (B), JP373.3 (B), JP393.3 (B)
Pin_33: J11.8, J12.8, J13.8, J14.8, J15.8, J16.8, J17.8, J18.8, J19.8, J20.8, J38.8, J39.8, J40.8, J41.8, J42.8, J43.8, J44.8, J45.8, J46.8, J47.8, JP10.3 (B), JP30.3 (B), JP50.3 (B), JP70.3 (B), JP90.3 (B), JP110.3 (B), JP130.3 (B), JP150.3 (B), JP170.3 (B), JP190.3 (B), JP212.3 (B), JP232.3 (B), JP252.3 (B), JP272.3 (B), JP292.3 (B), JP312.3 (B), JP332.3 (B), JP352.3 (B), JP372.3 (B), JP392.3 (B)
Pin_34: J11.7, J12.7, J13.7, J14.7, J15.7, J16.7, J17.7, J18.7, J19.7, J20.7, J38.7, J39.7, J40.7, J41.7, J42.7, J43.7, J44.7, J45.7, J46.7, J47.7, JP9.3 (B), JP29.3 (B), JP49.3 (B), JP69.3 (B), JP89.3 (B), JP109.3 (B), JP129.3 (B), JP149.3 (B), JP169.3 (B), JP189.3 (B), JP211.3 (B), JP231.3 (B), JP251.3 (B), JP271.3 (B), JP291.3 (B), JP311.3 (B), JP331.3 (B), JP351.3 (B), JP371.3 (B), JP391.3 (B)
Pin_35: J11.6, J12.6, J13.6, J14.6, J15.6, J16.6, J17.6, J18.6, J19.6, J20.6, J38.6, J39.6, J40.6, J41.6, J42.6, J43.6, J44.6, J45.6, J46.6, J47.6, JP8.3 (B), JP28.3 (B), JP48.3 (B), JP68.3 (B), JP88.3 (B), JP108.3 (B), JP128.3 (B), JP148.3 (B), JP168.3 (B), JP188.3 (B), JP210.3 (B), JP230.3 (B), JP250.3 (B), JP270.3 (B), JP290.3 (B), JP310.3 (B), JP330.3 (B), JP350.3 (B), JP370.3 (B), JP390.3 (B)
Pin_36: J11.5, J12.5, J13.5, J14.5, J15.5, J16.5, J17.5, J18.5, J19.5, J20.5, J38.5, J39.5, J40.5, J41.5, J42.5, J43.5, J44.5, J45.5, J46.5, J47.5, JP7.3 (B), JP27.3 (B), JP47.3 (B), JP67.3 (B), JP87.3 (B), JP107.3 (B), JP127.3 (B), JP147.3 (B), JP167.3 (B), JP187.3 (B), JP209.3 (B), JP229.3 (B), JP249.3 (B), JP269.3 (B), JP289.3 (B), JP309.3 (B), JP329.3 (B), JP349.3 (B), JP369.3 (B), JP389.3 (B)
Pin_37: J11.4, J12.4, J13.4, J14.4, J15.4, J16.4, J17.4, J18.4, J19.4, J20.4, J38.4, J39.4, J40.4, J41.4, J42.4, J43.4, J44.4, J45.4, J46.4, J47.4, JP6.3 (B), JP26.3 (B), JP46.3 (B), JP66.3 (B), JP86.3 (B), JP106.3 (B), JP126.3 (B), JP146.3 (B), JP166.3 (B), JP186.3 (B), JP208.3 (B), JP228.3 (B), JP248.3 (B), JP268.3 (B), JP288.3 (B), JP308.3 (B), JP328.3 (B), JP348.3 (B), JP368.3 (B), JP388.3 (B)
Pin_38: J11.3, J12.3, J13.3, J14.3, J15.3, J16.3, J17.3, J18.3, J19.3, J20.3, J38.3, J39.3, J40.3, J41.3, J42.3, J43.3, J44.3, J45.3, J46.3, J47.3, JP5.3 (B), JP25.3 (B), JP45.3 (B), JP65.3 (B), JP85.3 (B), JP105.3 (B), JP125.3 (B), JP145.3 (B), JP165.3 (B), JP185.3 (B), JP207.3 (B), JP227.3 (B), JP247.3 (B), JP267.3 (B), JP287.3 (B), JP307.3 (B), JP327.3 (B), JP347.3 (B), JP367.3 (B), JP387.3 (B)
Pin_39: J11.2, J12.2, J13.2, J14.2, J15.2, J16.2, J17.2, J18.2, J19.2, J20.2, J38.2, J39.2, J40.2, J41.2, J42.2, J43.2, J44.2, J45.2, J46.2, J47.2, JP4.3 (B), JP24.3 (B), JP44.3 (B), JP64.3 (B), JP84.3 (B), JP104.3 (B), JP124.3 (B), JP144.3 (B), JP164.3 (B), JP184.3 (B), JP206.3 (B), JP226.3 (B), JP246.3 (B), JP266.3 (B), JP286.3 (B), JP306.3 (B), JP326.3 (B), JP346.3 (B), JP366.3 (B), JP386.3 (B)
Pin_40: J11.1, J12.1, J13.1, J14.1, J15.1, J16.1, J17.1, J18.1, J19.1, J20.1, J38.1, J39.1, J40.1, J41.1, J42.1, J43.1, J44.1, J45.1, J46.1, J47.1, JP3.3 (B), JP23.3 (B), JP43.3 (B), JP63.3 (B), JP83.3 (B), JP103.3 (B), JP123.3 (B), JP143.3 (B), JP163.3 (B), JP183.3 (B), JP205.3 (B), JP225.3 (B), JP245.3 (B), JP265.3 (B), JP285.3 (B), JP305.3 (B), JP325.3 (B), JP345.3 (B), JP365.3 (B), JP385.3 (B)

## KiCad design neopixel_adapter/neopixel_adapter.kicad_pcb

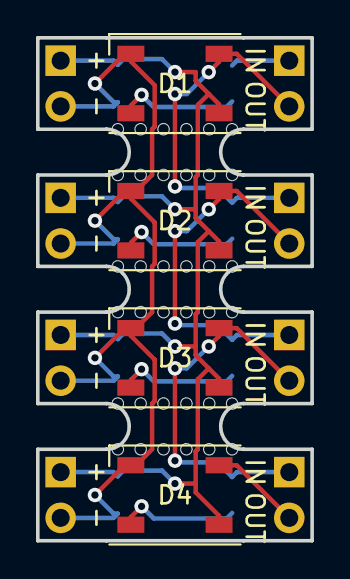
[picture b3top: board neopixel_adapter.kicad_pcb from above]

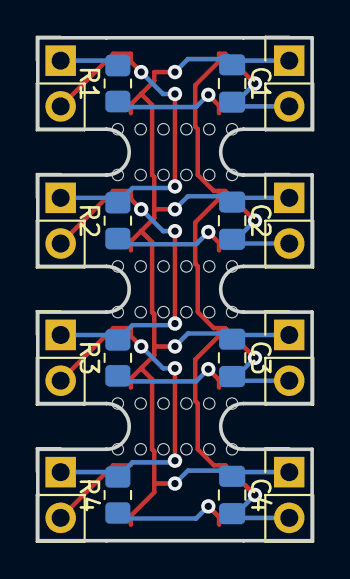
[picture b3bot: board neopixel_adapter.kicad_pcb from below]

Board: 2 copper layers, 15.2 x 27.9 mm, 20 parts (16 on the bottom side), 11 nets.

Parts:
C1, C2, C3, C4: 0.1uF; C_0805_2012Metric_Pad1.18x1.45mm_HandSolder
D1, D2, D3, D4: WS2812B; LED_WS2812B_PLCC4_5.0x5.0mm_P3.2mm
J1, J2, J3, J4, J5, J6, J7, J8: Conn_01x02; PinHeader_1x02_P2.54mm_Vertical
R1, R2, R3, R4: 470R; R_0805_2012Metric_Pad1.20x1.40mm_HandSolder

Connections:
/NeoPixel Module 1/DIN: J2.1, R1.1
/NeoPixel Module 1/DOUT: D1.2 (DOUT), J2.2, J4.1, R2.1
/NeoPixel Module 1/VDD: C1.2, C2.2, C3.2, C4.2, D1.1 (VDD), D2.1 (VDD), D3.1 (VDD), D4.1 (VDD), J1.1, J3.1, J5.1, J7.1
/NeoPixel Module 1/VSS: C1.1, C2.1, C3.1, C4.1, D1.3 (VSS), D2.3 (VSS), D3.3 (VSS), D4.3 (VSS), J1.2, J3.2, J5.2, J7.2
/NeoPixel Module 2/DOUT: D2.2 (DOUT), J4.2, J6.1, R3.1
/NeoPixel Module 3/DOUT: D3.2 (DOUT), J6.2, J8.1, R4.1
/NeoPixel Module 4/DOUT: D4.2 (DOUT), J8.2
unnamed: D1.4 (DIN), R1.2
unnamed: D2.4 (DIN), R2.2
unnamed: D3.4 (DIN), R3.2
unnamed: D4.4 (DIN), R4.2
